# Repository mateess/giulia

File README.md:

# Giulia
### 40% keyboard project

This will hopefully one day be a complete keyboard.  
Software side is USBaspLoader into QMK  
Inspired by coseyfannitutti's through-hole kits, but with some changes:
- Unistagger layout (like UT47)
- No sandwich, just PCB tray-mounted in a 3D printed lowpro case
- Despite being 40%, uses a "big" ATMega32A controller in DIP
- RGB underglow
- OLED to be admired by non-keeb people and possibly be useful for _stuff_

#### Credit/libraries used:
[Digikey](https://github.com/Digi-Key/digikey-kicad-library) - Molex USB connector  
[foostan](https://github.com/foostan/kbd) - OLED  
[ai03](https://github.com/ai03-2725/MX_Alps_Hybrid) - MX/ALPS switch

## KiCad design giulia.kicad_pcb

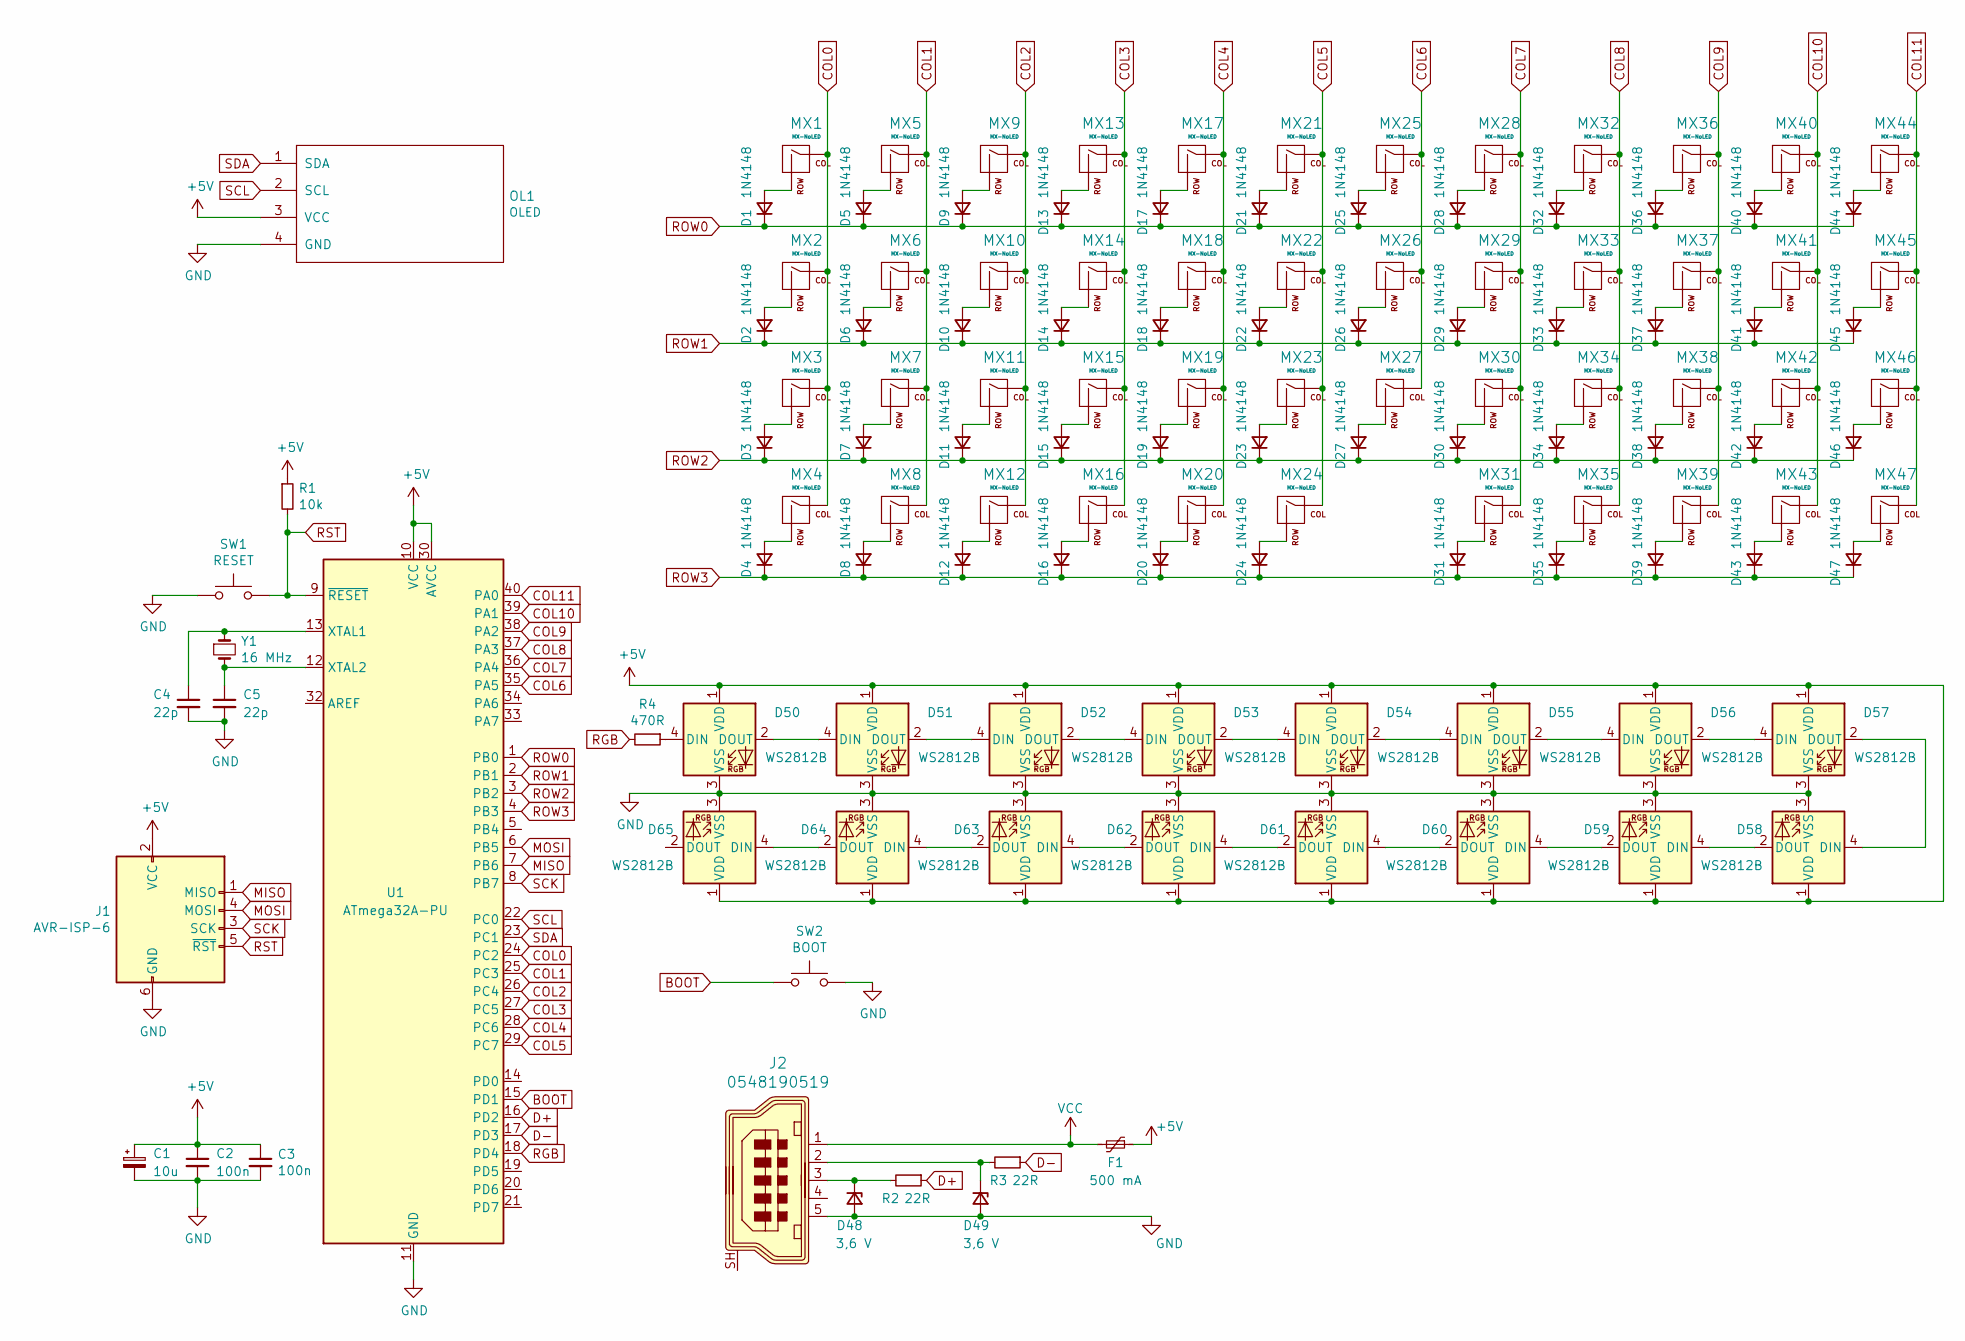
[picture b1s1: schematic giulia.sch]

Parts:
C1: 10u; CP_Radial_D5.0mm_P2.00mm
C2, C3: 100n; C_Disc_D5.0mm_W2.5mm_P5.00mm
C4, C5: 22p; C_Disc_D5.0mm_W2.5mm_P5.00mm
D1, D2, D3, D4, D5, D6, D7, D8, D9, D10, D11, D12, D13, D14, D15, D16, D17, D18, D19, D20, D21, D22, D23, D24, D25, D26, D27, D28, D29, D30, D31, D32, D33, D34, D35, D36, D37, D38, D39, D40, D41, D42, D43, D44, D45, D46, D47: 1N4148; D_DO-35_SOD27_P7.62mm_Horizontal_Giulia
D48, D49: 3,6 V; D_DO-35_SOD27_P7.62mm_Zener
D50, D51, D52, D53, D54, D55, D56, D57, D58, D59, D60, D61, D62, D63, D64, D65: WS2812B; LED_WS2812B_PLCC4_5.0x5.0mm_P3.2mm
F1: 500 mA; Fuse_BelFuse_0ZRE0005FF_L8.3mm_W3.8mm
J1: AVR-ISP-6; PinHeader_2x03_P2.54mm_Vertical
J2: 0548190519; USB_Mini_B_Female_548190519; MPN 0548190519; Digi-Key_PN WM17115-ND
MX1, MX4, MX5, MX6, MX7, MX8, MX9, MX10, MX11, MX12, MX13, MX14, MX15, MX16, MX17, MX18, MX19, MX21, MX22, MX23, MX25, MX26, MX27, MX28, MX29, MX30, MX32, MX33, MX34, MX35, MX36, MX37, MX38, MX39, MX40, MX41, MX42, MX43, MX46, MX47: MX-NoLED; MX-1U-NoLED
MX2, MX20, MX31, MX45: MX-NoLED; MX-1.25U-NoLED
MX3, MX44: MX-NoLED; MX-1.5U-NoLED
MX24: MX-NoLED; MX-2U-ReversedStabilizers-NoLED
OL1: OLED
R1: 10k; R_Axial_DIN0207_L6.3mm_D2.5mm_P10.16mm_Horizontal
R2, R3: 22R; R_Axial_DIN0207_L6.3mm_D2.5mm_P10.16mm_Horizontal
R4: 470R; R_Axial_DIN0207_L6.3mm_D2.5mm_P10.16mm_Horizontal
SW1: RESET; SW_PUSH_6mm
SW2: BOOT; SW_PUSH_6mm
U1: ATmega32A-PU; DIP-40_W15.24mm
Y1: 16 MHz; Crystal_HC49-U_Vertical

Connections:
+5V: C1.1, C2.1, C3.1, D50.1 (VDD), D51.1 (VDD), D52.1 (VDD), D53.1 (VDD), D54.1 (VDD), D55.1 (VDD), D56.1 (VDD), D57.1 (VDD), D58.1 (VDD), D59.1 (VDD), D60.1 (VDD), D61.1 (VDD), D62.1 (VDD), D63.1 (VDD), D64.1 (VDD), D65.1 (VDD), F1.1, J1.2 (VCC), OL1.3 (VCC), R1.1, U1.10 (VCC), U1.30 (AVCC)
BOOT: SW2.1, U1.15 (PD1)
COL0: MX1.1 (COL), MX2.1 (COL), MX3.1 (COL), MX4.1 (COL), U1.24 (PC2)
COL1: MX5.1 (COL), MX6.1 (COL), MX7.1 (COL), MX8.1 (COL), U1.25 (PC3)
COL2: MX9.1 (COL), MX10.1 (COL), MX11.1 (COL), MX12.1 (COL), U1.26 (PC4)
COL3: MX13.1 (COL), MX14.1 (COL), MX15.1 (COL), MX16.1 (COL), U1.27 (PC5)
COL4: MX17.1 (COL), MX18.1 (COL), MX19.1 (COL), MX20.1 (COL), U1.28 (PC6)
COL5: MX21.1 (COL), MX22.1 (COL), MX23.1 (COL), MX24.1 (COL), U1.29 (PC7)
COL6: MX25.1 (COL), MX26.1 (COL), MX27.1 (COL), U1.35 (PA5)
COL7: MX28.1 (COL), MX29.1 (COL), MX30.1 (COL), MX31.1 (COL), U1.36 (PA4)
COL8: MX32.1 (COL), MX33.1 (COL), MX34.1 (COL), MX35.1 (COL), U1.37 (PA3)
COL9: MX36.1 (COL), MX37.1 (COL), MX38.1 (COL), MX39.1 (COL), U1.38 (PA2)
COL10: MX40.1 (COL), MX41.1 (COL), MX42.1 (COL), MX43.1 (COL), U1.39 (PA1)
COL11: MX44.1 (COL), MX45.1 (COL), MX46.1 (COL), MX47.1 (COL), U1.40 (PA0)
D+: R2.1, U1.16 (PD2)
D-: R3.1, U1.17 (PD3)
GND: C1.2, C2.2, C3.2, C4.2, C5.2, D48.2 (A), D49.2 (A), D50.3 (VSS), D51.3 (VSS), D52.3 (VSS), D53.3 (VSS), D54.3 (VSS), D55.3 (VSS), D56.3 (VSS), D57.3 (VSS), D58.3 (VSS), D59.3 (VSS), D60.3 (VSS), D61.3 (VSS), D62.3 (VSS), D63.3 (VSS), D64.3 (VSS), D65.3 (VSS), J1.6 (GND), J2.5, OL1.4 (GND), SW1.1, SW2.2, U1.11 (GND), U1.31 (GND)
MISO: J1.1 (MISO), U1.7 (PB6)
MOSI: J1.4 (MOSI), U1.6 (PB5)
unnamed: C4.1, U1.13 (XTAL1), Y1.1
unnamed: C5.1, U1.12 (XTAL2), Y1.2
unnamed: D1.2 (A), MX1.2 (ROW)
unnamed: D2.2 (A), MX2.2 (ROW)
unnamed: D3.2 (A), MX3.2 (ROW)
unnamed: D4.2 (A), MX4.2 (ROW)
unnamed: D5.2 (A), MX5.2 (ROW)
unnamed: D6.2 (A), MX6.2 (ROW)
unnamed: D7.2 (A), MX7.2 (ROW)
unnamed: D8.2 (A), MX8.2 (ROW)
unnamed: D9.2 (A), MX9.2 (ROW)
unnamed: D10.2 (A), MX10.2 (ROW)
unnamed: D11.2 (A), MX11.2 (ROW)
unnamed: D12.2 (A), MX12.2 (ROW)
unnamed: D13.2 (A), MX13.2 (ROW)
unnamed: D14.2 (A), MX14.2 (ROW)
unnamed: D15.2 (A), MX15.2 (ROW)
unnamed: D16.2 (A), MX16.2 (ROW)
unnamed: D17.2 (A), MX17.2 (ROW)
unnamed: D18.2 (A), MX18.2 (ROW)
unnamed: D19.2 (A), MX19.2 (ROW)
unnamed: D20.2 (A), MX20.2 (ROW)
unnamed: D21.2 (A), MX21.2 (ROW)
unnamed: D22.2 (A), MX22.2 (ROW)
unnamed: D23.2 (A), MX23.2 (ROW)
unnamed: D24.2 (A), MX24.2 (ROW)
unnamed: D25.2 (A), MX25.2 (ROW)
unnamed: D26.2 (A), MX26.2 (ROW)
unnamed: D27.2 (A), MX27.2 (ROW)
unnamed: D28.2 (A), MX28.2 (ROW)
unnamed: D29.2 (A), MX29.2 (ROW)
unnamed: D30.2 (A), MX30.2 (ROW)
unnamed: D31.2 (A), MX31.2 (ROW)
unnamed: D32.2 (A), MX32.2 (ROW)
unnamed: D33.2 (A), MX33.2 (ROW)
unnamed: D34.2 (A), MX34.2 (ROW)
unnamed: D35.2 (A), MX35.2 (ROW)
unnamed: D36.2 (A), MX36.2 (ROW)
unnamed: D37.2 (A), MX37.2 (ROW)
unnamed: D38.2 (A), MX38.2 (ROW)
unnamed: D39.2 (A), MX39.2 (ROW)
unnamed: D40.2 (A), MX40.2 (ROW)
unnamed: D41.2 (A), MX41.2 (ROW)
unnamed: D42.2 (A), MX42.2 (ROW)
unnamed: D43.2 (A), MX43.2 (ROW)
unnamed: D44.2 (A), MX44.2 (ROW)
unnamed: D45.2 (A), MX45.2 (ROW)
unnamed: D46.2 (A), MX46.2 (ROW)
unnamed: D47.2 (A), MX47.2 (ROW)
unnamed: D48.1 (K), J2.3, R2.2
unnamed: D49.1 (K), J2.2, R3.2
unnamed: D50.2 (DOUT), D51.4 (DIN)
unnamed: D50.4 (DIN), R4.1
unnamed: D51.2 (DOUT), D52.4 (DIN)
unnamed: D52.2 (DOUT), D53.4 (DIN)
unnamed: D53.2 (DOUT), D54.4 (DIN)
unnamed: D54.2 (DOUT), D55.4 (DIN)
unnamed: D55.2 (DOUT), D56.4 (DIN)
unnamed: D56.2 (DOUT), D57.4 (DIN)
unnamed: D57.2 (DOUT), D58.4 (DIN)
unnamed: D58.2 (DOUT), D59.4 (DIN)
unnamed: D59.2 (DOUT), D60.4 (DIN)
unnamed: D60.2 (DOUT), D61.4 (DIN)
unnamed: D61.2 (DOUT), D62.4 (DIN)
unnamed: D62.2 (DOUT), D63.4 (DIN)
unnamed: D63.2 (DOUT), D64.4 (DIN)
unnamed: D64.2 (DOUT), D65.4 (DIN)
RGB: R4.2, U1.18 (PD4)
ROW0: D1.1 (K), D5.1 (K), D9.1 (K), D13.1 (K), D17.1 (K), D21.1 (K), D25.1 (K), D28.1 (K), D32.1 (K), D36.1 (K), D40.1 (K), D44.1 (K), U1.1 (PB0)
ROW1: D2.1 (K), D6.1 (K), D10.1 (K), D14.1 (K), D18.1 (K), D22.1 (K), D26.1 (K), D29.1 (K), D33.1 (K), D37.1 (K), D41.1 (K), D45.1 (K), U1.2 (PB1)
ROW2: D3.1 (K), D7.1 (K), D11.1 (K), D15.1 (K), D19.1 (K), D23.1 (K), D27.1 (K), D30.1 (K), D34.1 (K), D38.1 (K), D42.1 (K), D46.1 (K), U1.3 (PB2)
ROW3: D4.1 (K), D8.1 (K), D12.1 (K), D16.1 (K), D20.1 (K), D24.1 (K), D31.1 (K), D35.1 (K), D39.1 (K), D43.1 (K), D47.1 (K), U1.4 (PB3)
RST: J1.5 (~RST), R1.2, SW1.2, U1.9 (~RESET)
SCK: J1.3 (SCK), U1.8 (PB7)
SCL: OL1.2 (SCL), U1.22 (PC0)
SDA: OL1.1 (SDA), U1.23 (PC1)
VCC: F1.2, J2.1

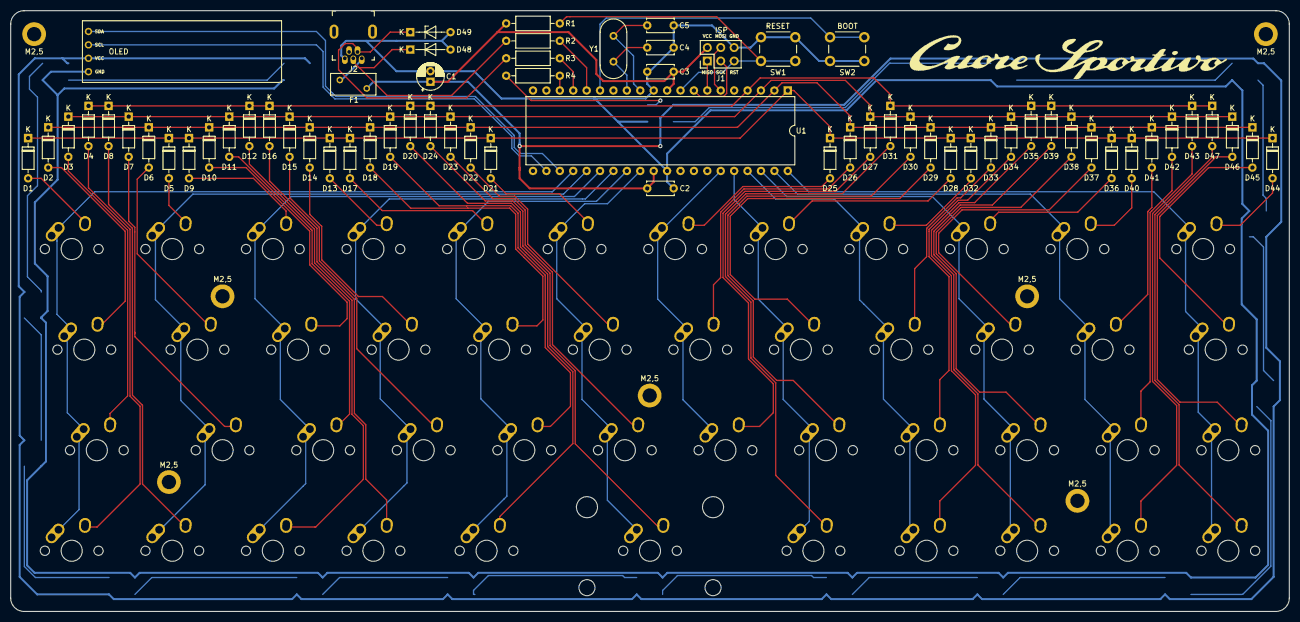
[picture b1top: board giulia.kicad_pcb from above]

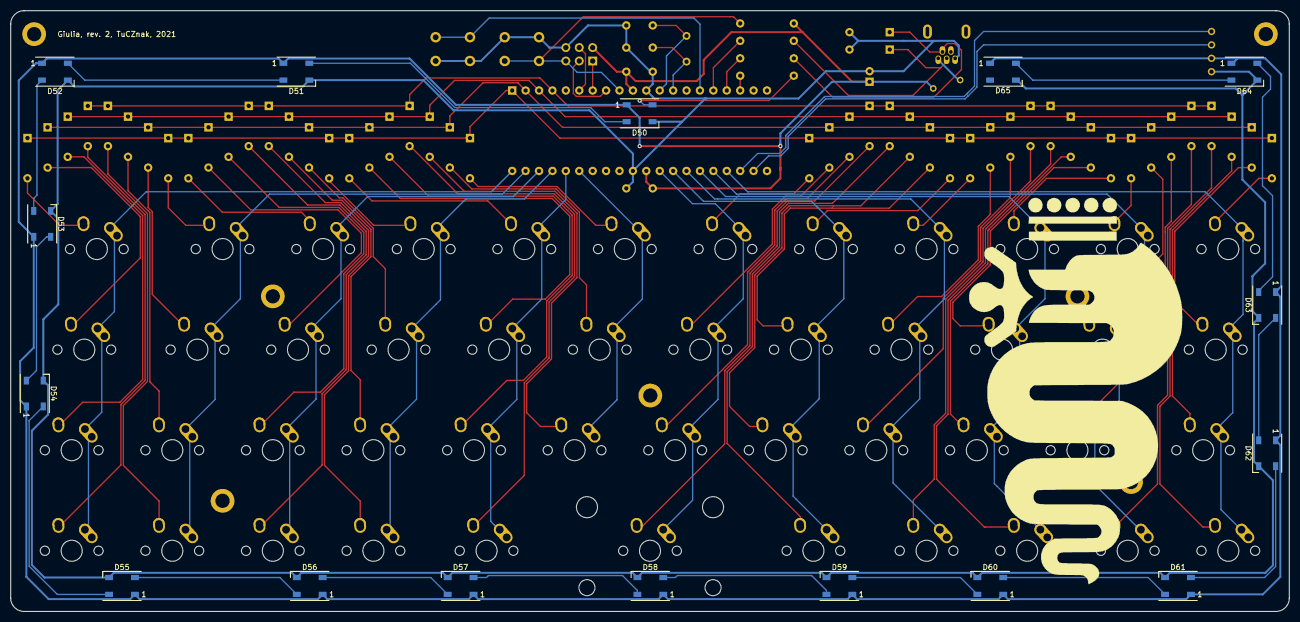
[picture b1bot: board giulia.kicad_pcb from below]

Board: 2 copper layers, 242.2 x 113.8 mm, 138 parts (16 on the bottom side), 96 nets.

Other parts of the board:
G1: LOGO; Cuore_Sportivo
G2: LOGO; Biscione
M2,5, M2,5#2, M2,5#3, M2,5#4, M2,5#5, M2,5#6, M2,5#7: MountingHole_2.7mm_M2.5_ISO7380_Pad

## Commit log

2021-07-20 Initialize project
2021-08-01 Add submodules
2021-08-01 project prep
2021-08-01 schematic start
2021-08-03 basic MCU wiring
2021-08-08 USB and ISP wiring
2021-08-08 added matrix
2021-08-09 minor adjustments
2021-08-09 add submodule
2021-08-09 schema hopefully complete
2021-08-09 minor schema stuff
2021-08-16 added most footprints
2021-08-16 all footprints assigned
2021-08-17 adjusted footprints
    changed some footprints based on common parts availability (carbon vs metallic resistors, ceramic condensator pin pitch)
2021-08-17 Started work on PCB footprints
2021-08-21 basic component layout
2021-08-25 Adjusting physical component layout
2021-08-25 PCB progress
    finally placed RGB footprints, added own footprint lib for easy silkscreen adjustment etc.
2021-08-25 cleaned up libs, removed submodules
2021-08-25 removed submodules
2021-08-25 the madness that is trace routing begins
2021-08-25 top layout that makes more sense
    imagine that, not using 20 vias for basic USB wiring
2021-08-27 routing progress, diode placement change
2021-08-27 switch routing done, fixed MCU position
2021-08-27 rev1 of routing done
2021-08-27 removed submodule
2021-08-27 moved USB footprint to own lib
2021-08-27 some PCB finishing touches
2021-08-27 redid column traces
    to be further away from pin support holes (just to be sure)
    also made the PCB a tiny bit larger for underglow trace safety
2021-08-28 rearranged RGB
2021-08-28 minor trace adjustments
2021-08-29 minor tweaks
2021-08-29 moved cols 4,5 to better pins
2021-08-29 moved resistors for visual alignment
2021-08-29 moved USB data lines
2021-08-29 final PCB rev1
2021-08-29 Gerbers for rev1 generated
2021-09-04 Added rev1 of lowpro case
    untested so far
2021-09-05 removed case files for now
    thing needs complete redesign on how parts are joined (who would have thought)
2021-09-12 fixed USB connector wiring
    The original prototype is wired backwards...
    Also moved boot button from B4 to D1, as having it on different port than USB seems to be giving the bootloader some trouble. This may get reversed if software fix is found.
2021-09-12 cosmetic adjustments
    since we're changing stuff anyway, might as well fix other minor things
2021-09-12 cosmetic adjustments
